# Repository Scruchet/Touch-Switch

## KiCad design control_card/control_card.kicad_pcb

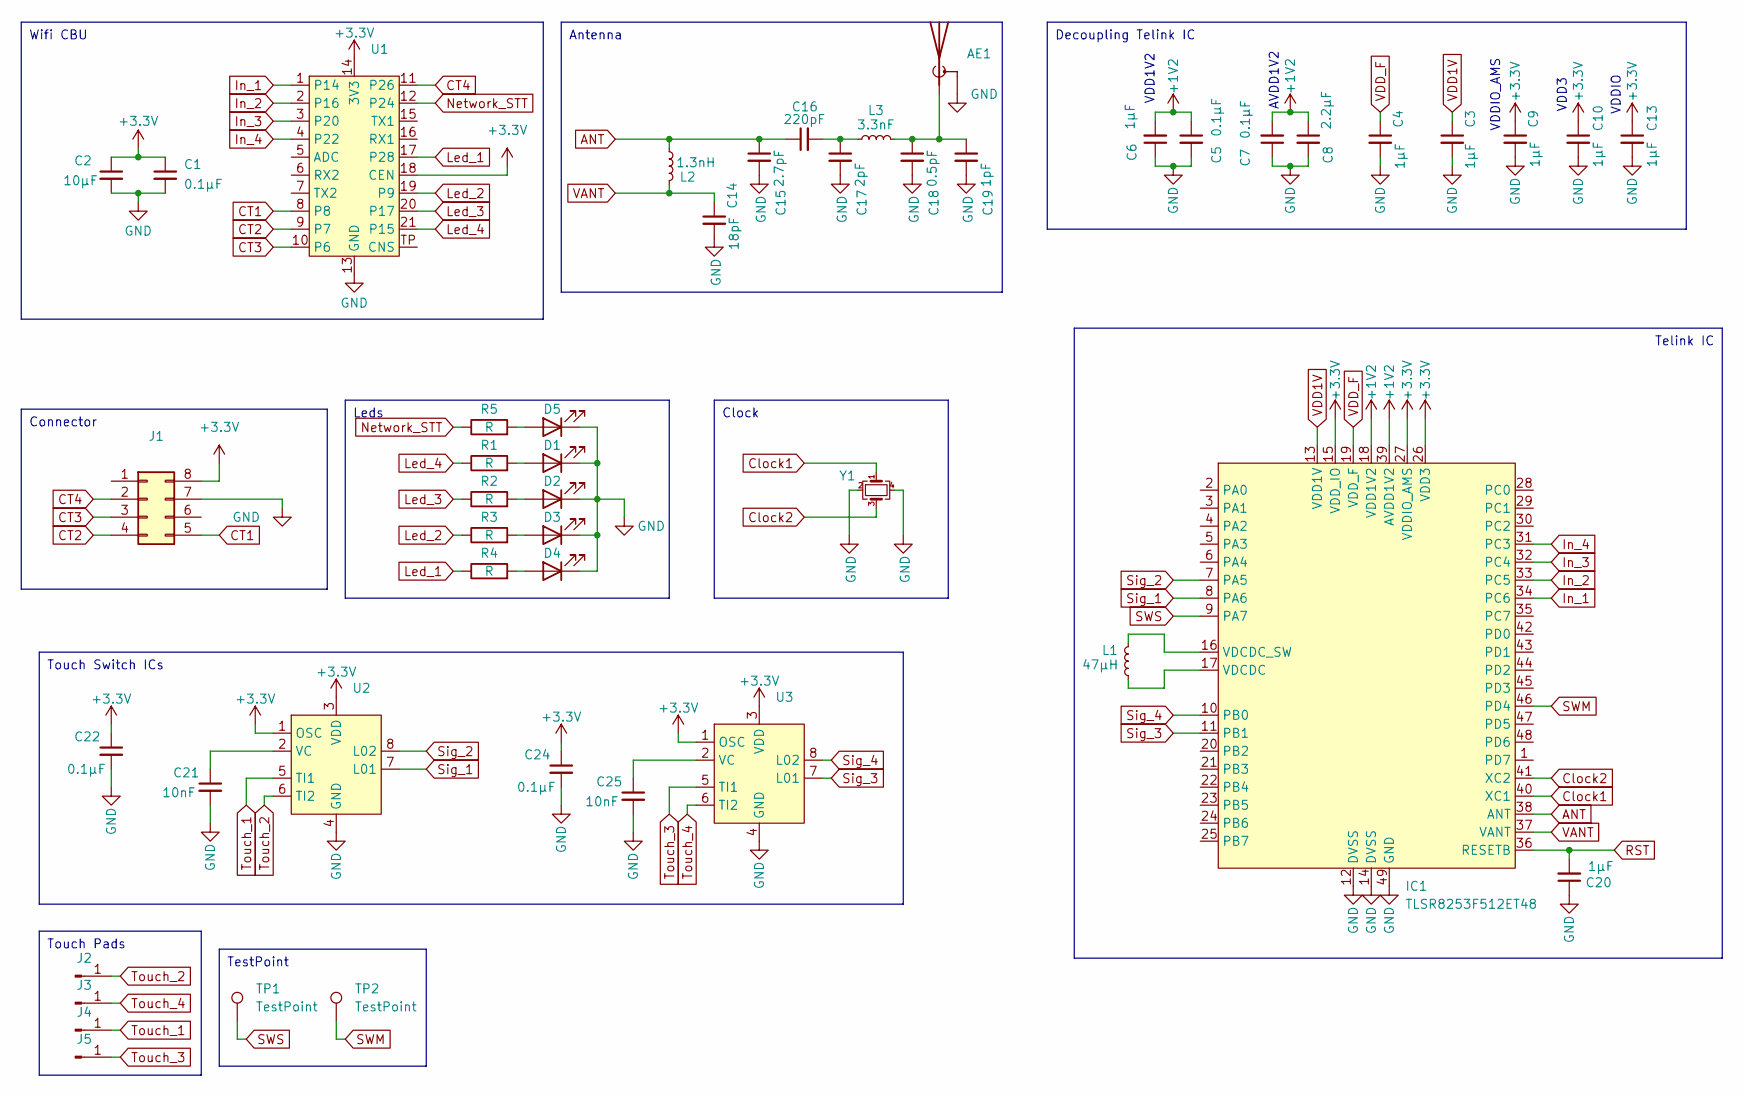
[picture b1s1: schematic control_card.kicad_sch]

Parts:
AE1: Antenna_Shield; Antenna
C1, C5, C7, C22, C24: 0.1µF; C_0603_1608Metric
C2: 10µF; C_0603_1608Metric
C3, C4, C6, C9, C10, C13, C20: 1µF; C_0603_1608Metric
C8: 2.2µF; C_0603_1608Metric
C14: 18pF; C_0603_1608Metric
C15: 2.7pF; C_0603_1608Metric
C16: 220pF; C_0603_1608Metric
C17: 2pF; C_0603_1608Metric
C18: 0.5pF; C_0603_1608Metric
C19: 1pF; C_0603_1608Metric
C21, C25: 10nF; C_0603_1608Metric
D1, D2, D3, D4, D5: LED; LED_0805_2012Metric
IC1: TLSR8253F512ET48; QFN-48-1EP_7x7mm_P0.5mm_EP5.6x5.6mm_ThermalVias; Mouser Part Number 141-TLSR8253F512ET32
J1: Conn_02x04_Counter_Clockwise; Male connector
J2, J3, J4, J5: Conn_01x01_Pin; Touch-Pad
L1: 47µH; L_0805_2012Metric
L2: 1.3nH; L_0402_1005Metric
L3: 3.3nF; L_0402_1005Metric
R1, R2, R3, R4, R5: R; R_0603_1608Metric
TP1, TP2: TestPoint; TestPoint_Pad_D1.0mm
U1: Wifi; Wifi CBU
U2, U3: SOIC-8_3.9x4.9mm_P1.27mm
Y1: Crystal_GND24_Small; Crystal_SMD_3225

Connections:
+1V2: C5.1, C6.2, C7.2, C8.1, IC1.18 (VDD1V2), IC1.39 (AVDD1V2)
+3.3V: C1.1, C2.1, C9.1, C10.1, C13.1, C22.1, C24.1, IC1.15 (VDD_IO), IC1.26 (VDD3), IC1.27 (VDDIO_AMS), J1.8, U1.14 (3V3), U1.18 (CEN), U2.1 (OSC), U2.3 (VDD), U3.1 (OSC), U3.3 (VDD)
ANT: C15.1, C16.1, IC1.38 (ANT), L2.1
CT1: J1.5, U1.8
CT2: J1.4, U1.9 (P7)
CT3: J1.3, U1.10 (P6)
CT4: J1.2, U1.11 (P26)
Clock1: IC1.40 (XC1), Y1.1
Clock2: IC1.41 (XC2), Y1.3
GND: AE1.2 (Shield), C1.2, C2.2, C3.2, C4.2, C5.2, C6.1, C7.1, C8.2, C9.2, C10.2, C13.2, C14.2, C15.2, C17.2, C18.2, C19.2, C20.1, C21.2, C22.2, C24.2, C25.2, D1.1 (K), D2.1 (K), D3.1 (K), D4.1 (K), D5.1 (K), IC1.12 (DVSS), IC1.14 (DVSS), IC1.49 (GND), J1.7, U1.13 (GND), U2.4 (GND), U3.4 (GND), Y1.2, Y1.4
In_1: IC1.34 (PC6), U1.1 (P14)
In_2: IC1.33 (PC5), U1.2 (P16)
In_3: IC1.32 (PC4), U1.3 (P20)
In_4: IC1.31 (PC3), U1.4 (P22)
Led_1: R4.1, U1.17 (P28)
Led_2: R3.1, U1.19 (P9)
Led_3: R2.1, U1.20 (P17)
Led_4: R1.1, U1.21 (P15)
unnamed: AE1.1 (A), C18.1, C19.1, L3.2
unnamed: C16.2, C17.1, L3.1
unnamed: D1.2 (A), R1.2
unnamed: D2.2 (A), R2.2
unnamed: D3.2 (A), R3.2
unnamed: D4.2 (A), R4.2
unnamed: D5.2 (A), R5.2
unnamed: IC1.17 (VDCDC), L1.1
unnamed: IC1.16 (VDCDC_SW), L1.2
unnamed: C21.1, U2.2 (VC)
unnamed: C25.1, U3.2 (VC)
Network_STT: R5.1, U1.12 (P24)
RST: C20.2, IC1.36 (RESETB)
SWM: IC1.46 (PD4), TP2.1; also elsewhere on the board
SWS: IC1.9 (PA7), TP1.1; also elsewhere on the board
Sig_1: IC1.8 (PA6), U2.7 (L01)
Sig_2: IC1.7 (PA5), U2.8 (L02)
Sig_3: IC1.11 (PB1), U3.7 (L01)
Sig_4: IC1.10 (PB0), U3.8 (L02)
Touch_1: J4.1, U2.5 (TI1)
Touch_2: J2.1, U2.6 (TI2)
Touch_3: J5.1, U3.5 (TI1)
Touch_4: J3.1, U3.6 (TI2)
VANT: C14.1, IC1.37 (VANT), L2.2
VDD1V: C3.1, IC1.13 (VDD1V)
VDD_F: C4.1, IC1.19 (VDD_F)

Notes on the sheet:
TestPoint
Antenna
Touch Switch ICs
Touch Pads
Leds
Wifi CBU
Connector
Clock
Decoupling Telink IC
Telink IC
AVDD1V2
VDD1V2
VDDIO
VDD3
VDDIO_AMS

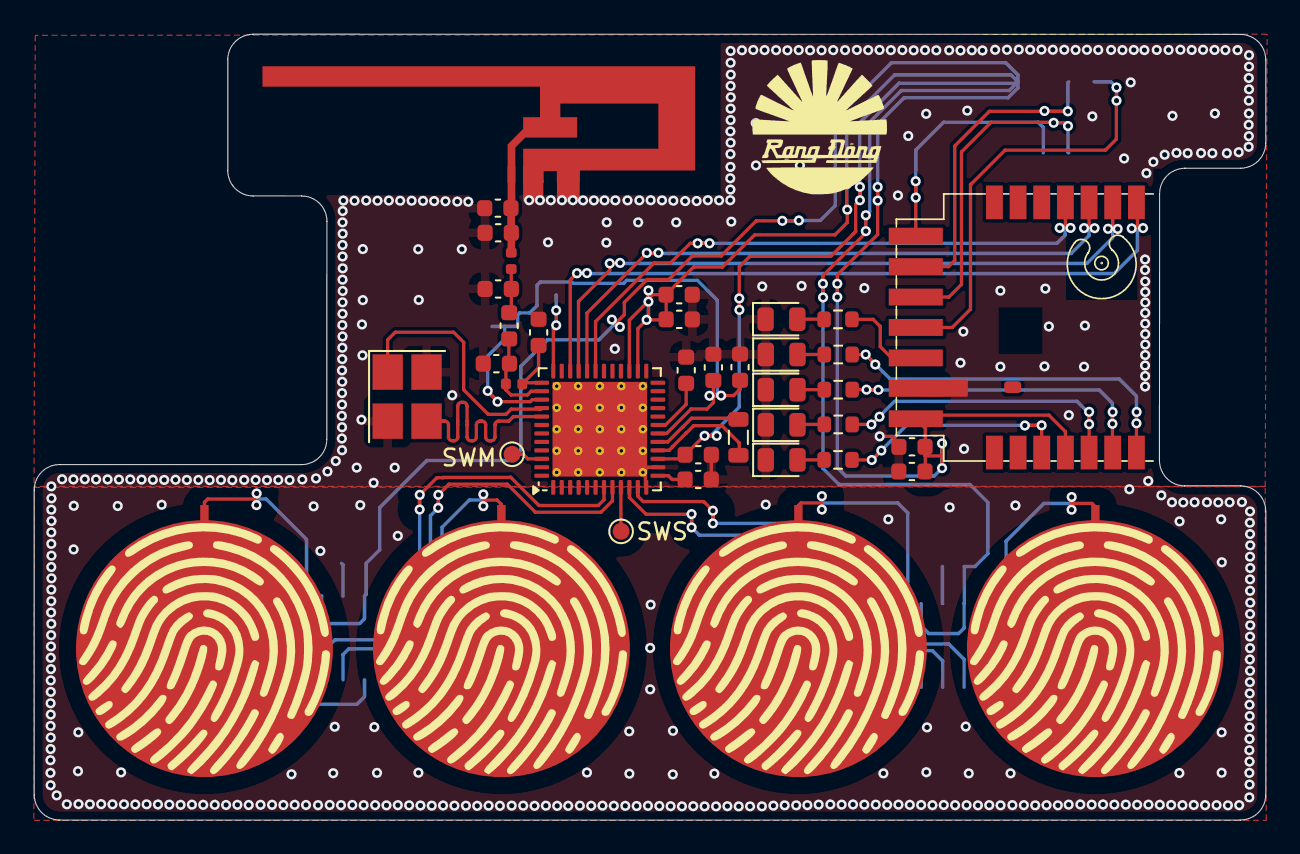
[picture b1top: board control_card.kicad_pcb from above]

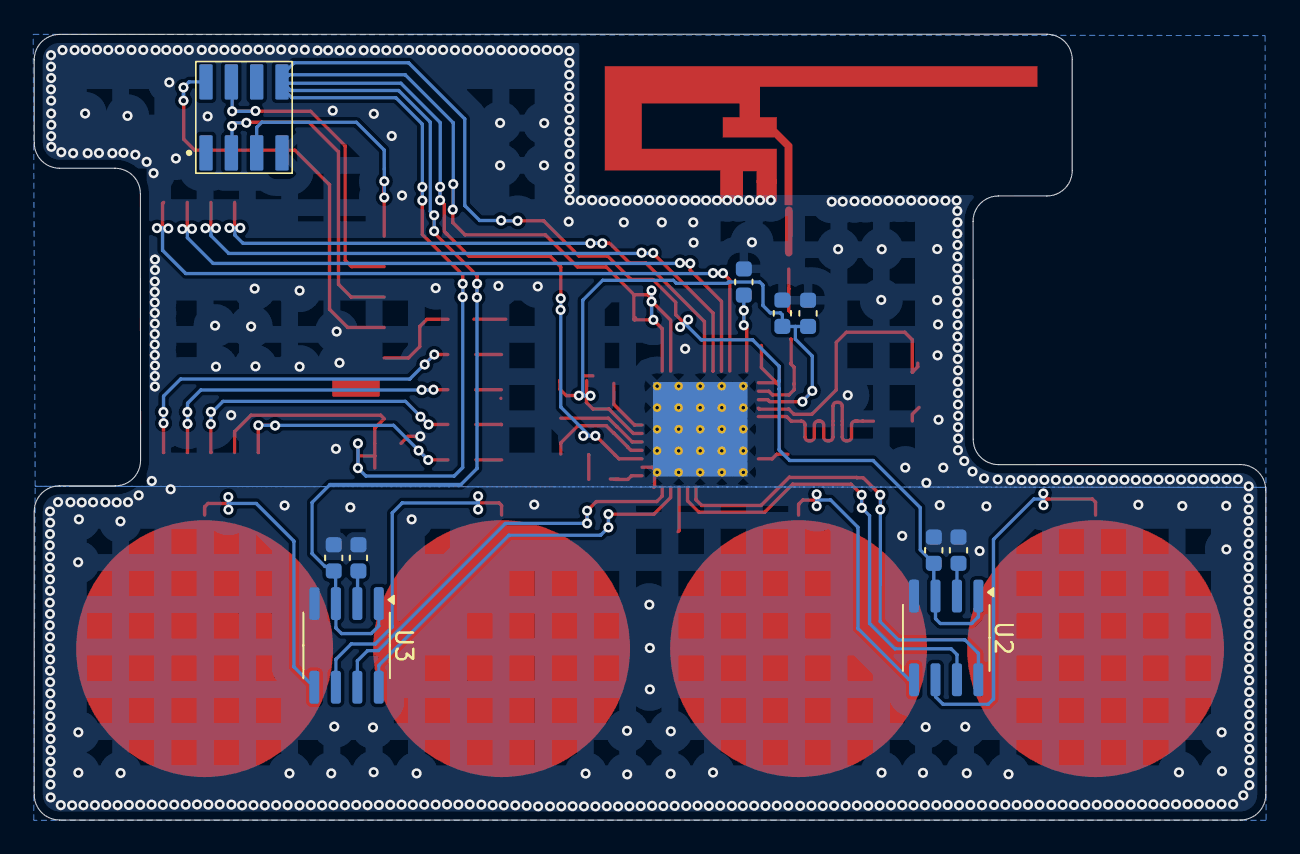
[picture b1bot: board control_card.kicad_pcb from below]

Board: 2 copper layers, 72.9 x 46.5 mm, 48 parts (10 on the bottom side), 44 nets.

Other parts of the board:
SWM: TestPoint; TestPoint_Pad_D1.0mm
SWS: TestPoint; TestPoint_Pad_D1.0mm

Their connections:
SWM: SWM.1; also elsewhere on the board
SWS: SWS.1; also elsewhere on the board

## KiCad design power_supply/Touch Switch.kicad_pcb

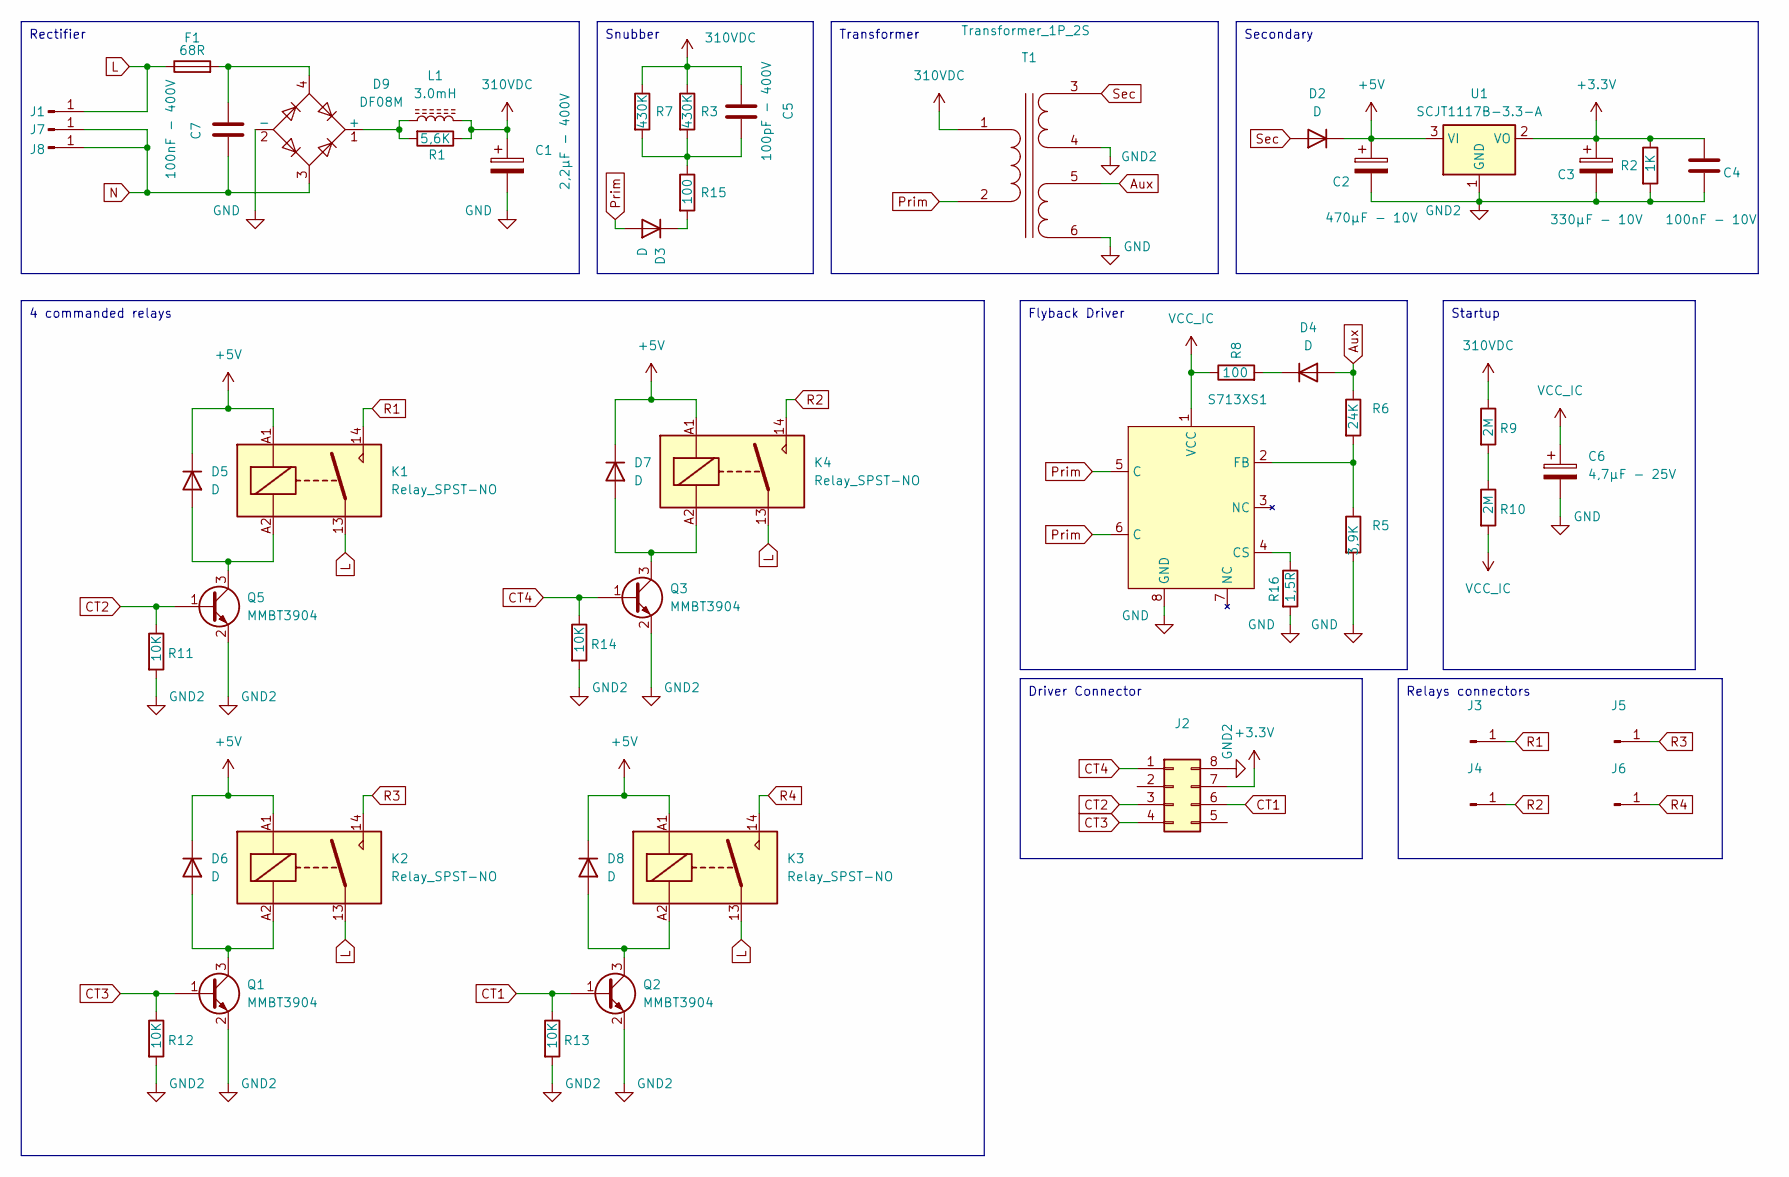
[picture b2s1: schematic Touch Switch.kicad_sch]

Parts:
C1: 2,2µF - 400V; CP_Radial_D8.0mm_P3.50mm
C2: 470µF - 10V; CP_Radial_D6.3mm_P2.50mm
C3: 330µF - 10V; CP_Radial_D6.3mm_P2.50mm
C4: 100nF - 10V; C_0805_2012Metric
C5: 100pF - 400V; C_1206_3216Metric
C6: 4,7µF - 25V; C_0805_2012Metric
C7: 100nF - 400V; MKP-X2-100NR10310
D2, D3, D4: D; D_SMA
D5, D6, D7, D8: D; D_SOD-123
D9: DF08M; Diode_Bridge_Diotec_ABS
F1: 68R; fuse
J1, J3, J4, J5, J6, J7, J8: Conn_01x01_Pin; power_connector
J2: Conn_02x04_Counter_Clockwise; Female connector
K1, K2, K3, K4: Relay_SPST-NO; relay
L1: 3.0mH; L_Radial_D7.5mm_P3.50mm_Fastron_07P
Q1, Q2, Q3, Q5: MMBT3904; SOT-23
R1: 5,6K; R_0805_2012Metric
R2: 1K; R_1206_3216Metric
R3, R7: 430K; R_1206_3216Metric
R5: 3,9K; R_0805_2012Metric
R6: 24K; R_0805_2012Metric
R8: 100; R_0805_2012Metric
R9, R10: 2M; R_1206_3216Metric
R11, R12, R13, R14: 10K; R_0805_2012Metric
R15: 100; R_1206_3216Metric
R16: 1,5R; R_1206_3216Metric
S713XS1: SOP-8_3.9x4.9mm_P1.27mm
T1: Transformer_1P_2S; transformer
U1: SCJT1117B-3.3-A; SOT-223-3_TabPin2

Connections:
310VDC: C1.1, C5.1, L1.2, R1.1, R3.1, R7.1, R9.1, T1.1 (AA)
+3.3V: C3.1, C4.1, J2.7, R2.1, U1.2 (VO)
+5V: C2.1, D2.1 (K), D5.1 (K), D6.1 (K), D7.1 (K), D8.1 (K), K1.A1, K2.A1, K3.A1, K4.A1, U1.3 (VI)
Aux: D4.2 (A), R6.1, T1.5 (SC)
CT1: J2.6, Q2.1 (B), R13.1
CT2: J2.3, Q5.1 (B), R11.1
CT3: J2.4, Q1.1 (B), R12.1
CT4: J2.1, Q3.1 (B), R14.1
GND: C1.2, C6.2, D9.2 (-), R5.2, R16.2, S713XS1.8 (GND), T1.6 (SD)
GND2: C2.2, C3.2, C4.2, J2.8, Q1.2 (E), Q2.2 (E), Q3.2 (E), Q5.2 (E), R2.2, R11.2, R12.2, R13.2, R14.2, T1.4 (SB), U1.1 (GND)
L: F1.1, J1.1, K1.13, K2.13, K3.13, K4.13
N: C7.2, D9.3, J7.1, J8.1
unnamed: C5.2, R3.2, R7.2, R15.1
unnamed: C7.1, D9.4, F1.2
unnamed: D3.1 (K), R15.2
unnamed: D4.1 (K), R8.2
unnamed: D5.2 (A), K1.A2, Q5.3 (C)
unnamed: D6.2 (A), K2.A2, Q1.3 (C)
unnamed: D7.2 (A), K4.A2, Q3.3 (C)
unnamed: D8.2 (A), K3.A2, Q2.3 (C)
unnamed: D9.1 (+), L1.1, R1.2
unnamed: R9.2, R10.1
unnamed: R16.1, S713XS1.4 (CS)
unnamed: R5.1, R6.2, S713XS1.2 (FB)
Prim: D3.2 (A), S713XS1.5 (C), S713XS1.6 (C), T1.2 (AB)
R1: J3.1, K1.14
R2: J4.1, K4.14
R3: J5.1, K2.14
R4: J6.1, K3.14
Sec: D2.2 (A), T1.3 (SA)
VCC_IC: C6.1, R8.1, R10.2, S713XS1.1 (VCC)

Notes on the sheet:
Transformer
Snubber
Startup
4 commanded relays
Relays connectors
Driver Connector
Rectifier
Secondary
Flyback Driver

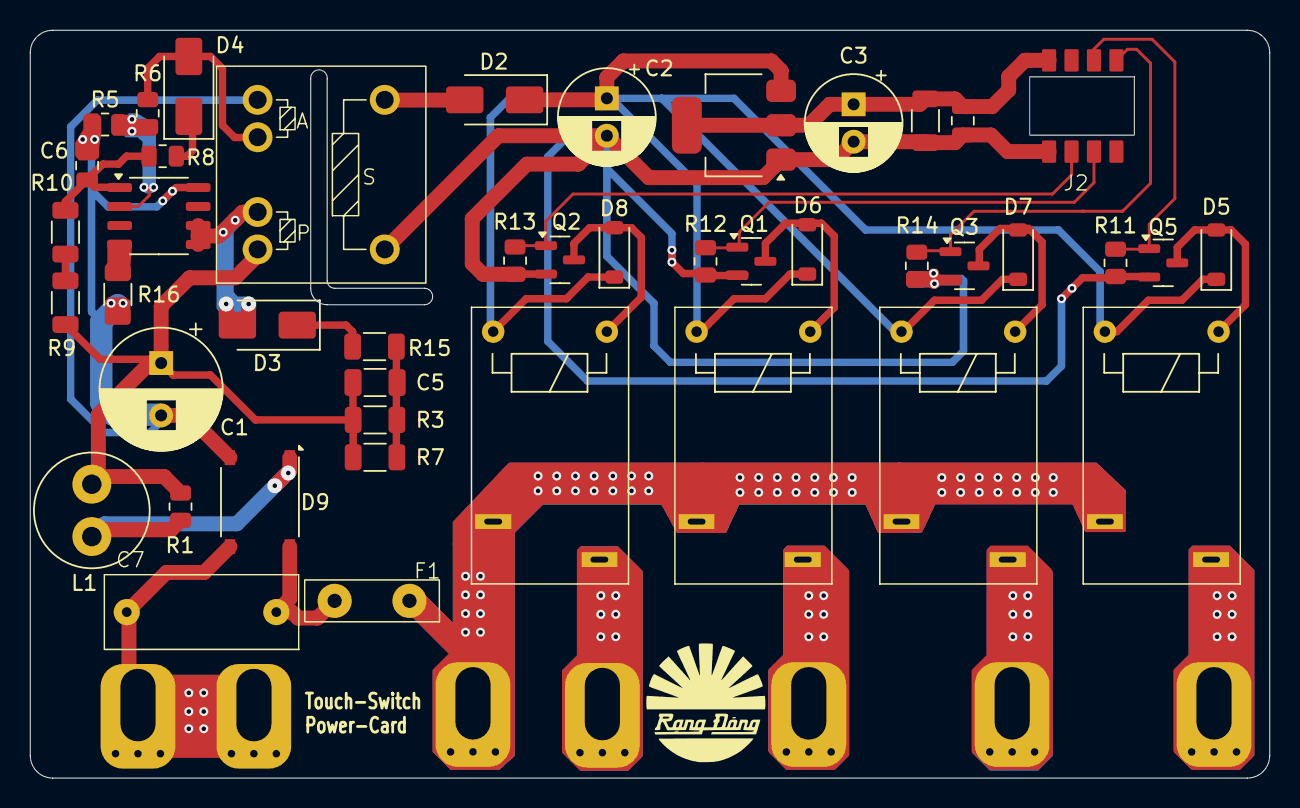
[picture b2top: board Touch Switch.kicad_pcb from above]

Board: 2 copper layers, 82.9 x 50.0 mm, 51 parts (0 on the bottom side), 31 nets.

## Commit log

2024-05-17 Schematic finished
2024-05-17 PCB started
2024-05-20 PCB V1
2024-05-20 PCB V2
2024-05-20 End 20-05-2024
2024-05-21 Secondary without GND PLANE
2024-05-23 PCB V3
2024-05-23 Reorganizing files in the project folder
2024-05-24 Modification : PCB
2024-05-24 Modified : PCB
2024-05-27 New Kicad Project + tree modified
2024-05-27 Control Card Started : Schematic & PCB
2024-05-28 PCB : started footprint and rooting
2024-05-28 PCB (control_card): Almost Finished
2024-05-29 PCB (control_card) : V1 finished
2024-05-29 PCB (control_card): V2 almost finished
2024-05-30 PCB (control_card) : V3 finished, perfect dimension
2024-05-30 PCB (control_card): ready for review
2024-05-31 PCB (control_card) : modified
2024-06-04 PCB (control_card) : Test point added
2024-06-04 PCB (control_card): modified
